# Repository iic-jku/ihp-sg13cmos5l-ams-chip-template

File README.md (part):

<!-- template-only -->
# An Open-Source Analog Mixed-Signal Chip Design Template & Tutorial for the ihp-sg13cmos5l Open-PDK

(c) 2026 Simon Dorrer and Harald Pretl

Institute for Integrated Circuits and Quantum Computing, Johannes Kepler University (JKU), Linz, Austria

<!-- /template-only -->
> [!IMPORTANT]
> This repository requires the [IIC-OSIC-TOOLS](https://github.com/iic-jku/IIC-OSIC-TOOLS) container with tag `2026.11` or later.

<!-- template-only -->
<p align="center">
  
  <br>
  <em>Chip render of the ihp-sg13cmos5l analog mixed-signal template chip (1.6 mm x 1.6 mm).</em>
</p>

<p align="center">
  
  <br>
  <em>Render of the TopMetal1 AMS Chip logo, generated with the tool ArtistIC.</em>
</p>

## Overview

Developing high-performance open-source silicon requires both the availability of tapeout-ready open-PDKs and robust, user-friendly EDA flows. While digital RTL-to-GDS flows offer an easy entry with documentation and examples, analog mixed-signal (AMS) design still suffers from a steep learning curve and the lack of examples and instructions. This repository provides a comprehensive template and tutorial for AMS chip design using the ihp-sg13cmos5l Open-PDK, guiding the designer from initial system-level specifications to the tapeout-ready chip.

This Makefile-driven repository simulates, builds, and fully verifies (DRC, LVS, PEX) a complete analog mixed-signal chip for the ihp-sg13cmos5l Open-PDK, including padframe generation, top-level assembly and bondplan generation. The flow uses:

- [**LibreLane**](https://github.com/librelane/librelane) for digital macro hardening, padframe generation, top-level assembly, filler and logo insertion
- [**Xschem**](https://github.com/StefanSchippers/xschem) for schematic entry
- [**Ngspice**](https://github.com/danchitnis/ngspice-sf-mirror), [**VACASK**](https://codeberg.org/arpadbuermen/VACASK) and [**CACE**](https://github.com/fossi-foundation/cace) for analog simulation
- [**KLayout**](https://github.com/KLayout/klayout) for viewing and routing of the layout
- [**Magic**](https://github.com/rtimothyedwards/magic) + [**Netgen**](https://github.com/rtimothyedwards/netgen) and [**KLayout**](https://github.com/KLayout/klayout) for DRC, LVS and PEX verification
- [**gdscheck**](https://github.com/aesc-silicon/gdscheck) as a third, standalone DRC engine with its own rule decks
- **SystemVerilog**, [**Verilator**](https://github.com/verilator/verilator), [**iverilog**](https://github.com/steveicarus/iverilog), [**cocotb**](https://github.com/cocotb/cocotb), [**GTKWave**](https://github.com/gtkwave/gtkwave) and [**Surfer**](https://gitlab.com/surfer-project/surfer) for linting and simulation of digital macros

The repository is the starting point for your own custom silicon and provides a universal design flow solution: Just clone the repo, enter the IIC-OSIC-TOOLS container, and run `make all` to get a tapeout-ready analog mixed-signal chip. Focus on your design and do not worry about the tools and the design flow!

Furthermore, it serves as a regression test for the above-mentioned open-source tools and their dependencies using the ihp-sg13cmos5l Open-PDK.

## PDKs

This template is available for the following open-source PDKs:
- **ihp-sg13g2**: [ihp-sg13g2-ams-chip-template](https://github.com/iic-jku/ihp-sg13g2-ams-chip-template)
- **ihp-sg13cmos5l**: this repository
- **sky130A**: [sky130A-ams-chip-template](https://github.com/iic-jku/sky130A-ams-chip-template)
- **gf180mcuD**: [gf180mcuD-ams-chip-template](https://github.com/iic-jku/gf180mcuD-ams-chip-template)

## Tutorial

A step-by-step tutorial, including additional exercises, can be found [here](https://iic-jku.github.io/ihp-sg13cmos5l-ams-chip-template/index.html). It is the SG13CMOS5L version of the [tutorial](https://iic-jku.github.io/ihp-sg13g2-ams-chip-template/index.html) of the SG13G2 sibling of this template.

An overview of the open-source IC design landscape is presented [here](https://ic3.ie/resources/open-source-ic-design-day).

Are you interested in an open-source RFIC flow? Check it out [here](https://github.com/iic-jku/SG13CMOS_SPARX).

## Examples

Examples based on the SG13G2 sibling of this template are:
- [TinyWhisper](https://github.com/iic-jku/TinyWhisper): An Open-Source Fully-Integrated Multi-Mode Short-Wave Transmitter for Amateur Radio Applications in 130-nm CMOS
- [SPARX](https://github.com/iic-jku/SG13CMOS_SPARX): An Open-Source, Automated, Programmatically Generated, Frequency-Scalable Six-Port Receiver in 130-nm CMOS
- [Multi-Project Chip](https://github.com/iic-jku/gf180mcu-jku-projects) for the wafer.space gf180mcuD MPW run

<!-- /template-only -->
## Chip Documentation

A designer-oriented description of this chip can be found in [doc/](doc/):

- **[doc/specifications.md](doc/specifications.md)**: top-level specifications (technology, supplies, clock, macro inventory, functional behaviour).
- **[doc/pinout.md](doc/pinout.md)**: full 32-pad bondpad table per side, with the `chip_top` port and the role each pad carries inside `chip_core`.
- **[doc/floorplan.md](doc/floorplan.md)**: die / core geometry, hard-macro placement coordinates, PDN strategy and the floorplan diagram.

Measurements of the fabricated chip go into [measurements/](measurements/), one folder per taped-out release.

## Directory Structure

<details>
<summary>Show Directory Structure</summary>

```text
📁 ihp-sg13cmos5l-ams-chip-template/
├─ 📁 .github/
│  └─ 📁 workflows/
│     ├─ license-check.yml
│     ├─ quarto-publish.yml
│     └─ regression.yml
├─ 📁 doc/
│  ├─ 📁 ihp-sg13cmos5l-Open-PDK/
│  ├─ 📁 ihp-structure-proposals/
│  ├─ 📁 klayout/
│  ├─ 📁 librelane/
│  ├─ 📁 prep-ic/
│  ├─ 📁 sizing/
│  ├─ 📁 verilog/
│  ├─ floorplan.md
│  ├─ pinout.md
│  ├─ README.md
│  └─ specifications.md
├─ 📁 flow/
│  ├─ 📁 artistic/
│  ├─ 📁 librelane/
│  │  ├─ 📁 plugins/
│  │  │  └─ librelane_plugin_chip_finish.py
│  │  ├─ chip_top.sdc
│  │  ├─ config.yaml
│  │  └─ pdn_cfg.tcl
│  └─ 📁 logo/
│     └─ chip_logo_mono.png
├─ 📁 ip/
│  ├─ 📁 sg13cmos5l_io_custom/
│  ├─ 📁 sg13cmos5l_ip__bondpad_70x70/
│  │  ├─ 📁 final/
│  │  ├─ 📁 script/
│  │  ├─ 📁 verification/
│  │  ├─ Makefile
│  │  └─ README.md
│  ├─ 📁 sg13cmos5l_ip__rfpad_70x70/
│  │  ├─ 📁 final/
│  │  ├─ 📁 netlist/
│  │  ├─ 📁 schematic/
│  │  ├─ 📁 script/
│  │  ├─ 📁 verification/
│  │  ├─ Makefile
│  │  └─ README.md
│  ├─ 📁 sg13cmos5l_ip__jku/
│  │  ├─ 📁 final/
│  │  ├─ 📁 logo/
│  │  ├─ 📁 script/
│  │  ├─ 📁 verification/
│  │  ├─ Makefile
│  │  └─ README.md
│  ├─ 📁 sg13cmos5l_ip__jku_names/
│  │  ├─ 📁 final/
│  │  ├─ 📁 logo/
│  │  ├─ 📁 script/
│  │  ├─ 📁 verification/
│  │  ├─ Makefile
│  │  └─ README.md
│  └─ 📁 sg13cmos5l_ip__template_name/
│     ├─ 📁 final/
│     ├─ 📁 logo/
│     ├─ 📁 script/
│     ├─ 📁 verification/
│     ├─ Makefile
│     └─ README.md
├─ 📁 layout/
│  ├─ chip_top.gds.gz
│  └─ chip_top_logo_fill.gds.gz
├─ 📁 LICENSES/
│  ├─ Apache-2.0.txt
│  ├─ LicenseRef-EUROPRACTICE.txt
│  └─ SHL-2.1.txt
├─ 📁 macros/
│  ├─ 📁 counter/
│  │  ├─ 📁 final/
│  │  ├─ 📁 flow/
│  │  ├─ 📁 fpga/
│  │  ├─ 📁 netlist/
│  │  ├─ 📁 render/
│  │  ├─ 📁 rtl/
│  │  ├─ 📁 schematic/
│  │  ├─ 📁 scripts/
│  │  ├─ 📁 testbenches/
│  │  ├─ 📁 verification/
│  │  ├─ Makefile
│  │  └─ README.md
│  ├─ 📁 inverter/
│  │  ├─ 📁 final/
│  │  ├─ 📁 layout/
│  │  ├─ 📁 netlist/
│  │  ├─ 📁 render/
│  │  ├─ 📁 schematic/
│  │  ├─ 📁 scripts/
│  │  ├─ 📁 testbenches/
│  │  ├─ 📁 verification/
│  │  ├─ Makefile
│  │  └─ README.md
│  ├─ 📁 scripts/
│  ├─ 📁 vco/
│  │  ├─ 📁 final/
│  │  ├─ 📁 layout/
│  │  ├─ 📁 netlist/
│  │  ├─ 📁 render/
│  │  ├─ 📁 schematic/
│  │  ├─ 📁 scripts/
│  │  ├─ 📁 testbenches/
│  │  ├─ 📁 verification/
│  │  ├─ Makefile
│  │  └─ README.md
│  ├─ Makefile
│  └─ README.md
├─ 📁 measurements/
│  ├─ 📁 v.1.0.0/
│  │  ├─ 📁 amplifier/
│  │  ├─ 📁 chip/
│  │  ├─ 📁 counters/
│  │  ├─ 📁 inverter/
│  │  ├─ 📁 ringosc/
│  │  ├─ 📁 vco/
│  │  └─ README.md
│  └─ README.md
├─ 📁 netlist/
│  ├─ 📁 layout/
│  ├─ 📁 nl/
│  ├─ 📁 pex/
│  ├─ 📁 pnl/
│  ├─ 📁 schematic/
│  ├─ 📁 sdc/
│  ├─ 📁 spef/
│  └─ 📁 spice/
├─ 📁 packaging/
│  ├─ 📁 layout/
│  │  ├─ chip_top_bondplan.gds
│  │  ├─ chip_top_logo_TM1.gds.gz
│  │  ├─ EP_PACKAGES_08022018.gds
│  │  └─ OP_QFN32_A4_FIT.gds
│  ├─ 📁 render/
│  │  └─ chip_top_bondplan_{white,black}.{png,svg}
│  ├─ 📁 scripts/
│  │  └─ run_bondplan.py
│  ├─ config.yaml
│  ├─ README.md
│  └─ result.md
├─ 📁 release/
│  └─ 📁 v.1.0.0/
│     ├─ 📁 gds/
│     ├─ 📁 img/
│     └─ 📁 netlist/
├─ 📁 render/
│  ├─ 📁 blender/
│  └─ 📁 img/
├─ 📁 rtl/
│  ├─ chip_core.sv
│  └─ chip_top.sv
├─ 📁 schematic/
│  └─ 📁 xschem/
│     ├─ chip_top.sch
│     ├─ chip_top.sym
│     ├─ chip_top_pex.sym
│     └─ xschemrc
├─ 📁 scripts/
│  ├─ check_pex_ports.py
│  └─ sim_gl_power.tcl
├─ 📁 testbenches/
│  ├─ 📁 cocotb/
│  │  ├─ chip_top_tb.gtkw
│  │  ├─ chip_top_tb.py
│  │  └─ chip_top_tb.surf.ron
│  └─ 📁 xschem/
│     ├─ 📁 plot_simulations/
│     │  ├─ 📁 data/
│     │  ├─ 📁 figures/
│     │  ├─ ngspice2python.py
│     │  └─ plot_chip_top.py
│     ├─ chip_top_tb_tran.sch
│     └─ xschemrc
├─ 📁 tutorial/
│  ├─ 📁 fig/
│  ├─ _quarto.yml
│  ├─ index.qmd
│  ├─ Makefile
│  └─ requirements.txt
├─ 📁 verification/
│  ├─ 📁 drc/
│  ├─ 📁 lvs/
│  └─ 📁 reports/
│     ├─ antenna_summary.rpt
│     ├─ antenna_violations.rpt
│     ├─ irdrop.rpt
│     ├─ lvs.netgen.rpt
│     ├─ manufacturability.rpt
│     ├─ sim_gl_power_cocotb.rpt
│     ├─ stapostpnr_*.rpt
│     ├─ stat.rpt
│     ├─ yosys_post_dff.rpt
│     ├─ yosys_pre_techmap.rpt
│     └─ yosys_synth_check.rpt
├─ CITATION.cff
├─ LICENSE
├─ Makefile
├─ README.md
├─ REUSE.toml
└─ ToDo.md
```

</details>

## Xschem Configuration

Xschem reads exactly one `xschemrc` at start-up, and that file decides which symbol libraries are visible and where netlists and simulation output are written. This repository ships one per folder that holds schematics:

| `xschemrc` | Belongs to |
| --- | --- |
| [`schematic/xschem/xschemrc`](schematic/xschem/xschemrc) | chip top-level schematics |
| [`testbenches/xschem/xschemrc`](testbenches/xschem/xschemrc) | chip top-level testbenches |
| [`ip/sg13cmos5l_ip__rfpad_70x70/schematic/xschem/xschemrc`](ip/sg13cmos5l_ip__rfpad_70x70/schematic/xschem/xschemrc) | RF pad schematic |
| [`macros/inverter/schematic/xschem/xschemrc`](macros/inverter/schematic/xschem/xschemrc) | inverter schematics |
| [`macros/inverter/testbenches/xschem/xschemrc`](macros/inverter/testbenches/xschem/xschemrc) | inverter testbenches |
| [`macros/inverter/verification/cace/templates/xschemrc`](macros/inverter/verification/cace/templates/xschemrc) | CACE testbench templates |
| [`macros/counter/schematic/xschem/xschemrc`](macros/counter/schematic/xschem/xschemrc) | counter schematics |
| [`macros/counter/testbenches/xschem/xschemrc`](macros/counter/testbenches/xschem/xschemrc) | counter testbenches |
| [`macros/vco/schematic/xschem/xschemrc`](macros/vco/schematic/xschem/xschemrc) | VCO schematics |
| [`macros/vco/testbenches/xschem/xschemrc`](macros/vco/testbenches/xschem/xschemrc) | VCO testbenches |

### What Every File Does

All of them run the same four steps, in this order:

1. **Pick the PDK.** `PDK_ROOT` is probed in the usual install locations if the environment does not set it, and `PDK` falls back to `ihp-sg13cmos5l`. The container already exports `PDK_ROOT`, and [`.designinit`](.designinit) exports `PDK`, so this step is only a safety net for an Xschem started outside that environment.
2. **Source the PDK `xschemrc`.** `$PDK_ROOT/$PDK/libs.tech/xschem/xschemrc` brings in the IHP device symbols, the ngspice model paths and the IHP menu. It is guarded by `[info exists PDK]` so it is read once even when several project files are chained.
3. **Add the project library paths.** `append_xschem_library_path_unique` appends a folder to `XSCHEM_LIBRARY_PATH` only if it is not already there, so the same folder never appears twice no matter how the files are chained. [`testbenches/xschem/xschemrc`](testbenches/xschem/xschemrc) adds none of its own and gets its paths from the file it sources.
4. **Pin the netlist directory.** `pin_netlist_dir` decides where `xschem netlist` and the simulators write.

Both helper procedures are defined behind an `[info commands ...]` guard, so sourcing one file from another is harmless and the order does not matter.

### How the Files Are Chained

The chip top-level pulls in everything below it:

```text
testbenches/xschem/xschemrc
└─ source schematic/xschem/xschemrc
   ├─ source macros/inverter/schematic/xschem/xschemrc
   └─ source macros/counter/schematic/xschem/xschemrc

macros/inverter/verification/cace/templates/xschemrc
└─ source macros/inverter/schematic/xschem/xschemrc
```

Each schematic folder puts itself and its sibling testbenches folder on the library path, and each testbenches folder does the reverse. The chip top-level therefore sees all six schematic and testbench folders, which is what lets `chip_top.sch` instantiate `inverter_top.sym` and `counter_top.sym`, and what lets you open a macro testbench from a chip top-level session. The macro files do not source each other, so a macro can be opened and simulated on its own without the top level being present.

### Where Netlists and Simulation Output Go

`pin_netlist_dir` maps the folder of the schematic being netlisted to a `simulations/` folder:

| Schematic lives in | `netlist_dir` |
| --- | --- |
| `<x>/testbenches/xschem` | `<x>/testbenches/xschem/simulations` |
| `<x>/schematic/xschem` | `<x>/testbenches/xschem/simulations` |
| `.../cace/templates` | `.../cace/templates/simulations` |
| anywhere else (a PDK example) | left at the value the `xschemrc` pinned |

It runs twice: once while the `xschemrc` is read, using that file's own folder, and again through Xschem's `load_file_postprocess` hook for every schematic that is opened afterwards. The second call is the important one. Because the chip top-level puts the macro folders on the library path, a macro testbench can be opened from a chip top-level session, and without the hook its netlist would land in `testbenches/xschem/simulations/`. Its relative includes such as `.include ../../../netlist/pex/inverter_magic_pex_3.spice` are resolved by ngspice relative to the netlist file, so they would then point at the wrong tree and the simulation would abort. With the hook, the netlist always lands next to its own schematic and the includes resolve.

A `set netlist_dir` passed on the Xschem command line still wins, because `--command` runs after the file is loaded. The LVS netlist targets rely on this to write into `netlist/schematic/` instead.

All `simulations/` folders are generated and git-ignored.

### Which File Is Used

- The Makefile targets always name one explicitly with `--rcfile`, so a target behaves the same from any working directory.
- Inside the container, [`.designinit`](.designinit) only exports the PDK variables. It does not wrap `xschem`, so a plain `xschem <file>` uses whatever the current directory provides.
- Starting Xschem from within one of the folders in the table above picks up that folder's file, which is the normal interactive case.
- `make open` starts Xschem in the file's own directory, so the same rule applies to every button of the file browser, see [Open the Design Files](#open-the-design-files).

## Makefile Structure

The whole flow is driven by Makefiles. The top-level `Makefile` builds the chip, and every component under [`macros/`](macros/) and [`ip/`](ip/) has its own `Makefile` and `README.md` following the same conventions (`make help`, `make all`, and so on). You can run each component from the top level or directly from inside its own folder. The figure below shows how the targets are connected when you run `make all` at the top level.

<p align="center">
  
  <br>
  <em>Overview of the Makefile targets.</em>
</p>

Every coloured branch corresponds to one deliverable (top chip, bondpad, RF pad, logos, digital macro, analog macro, packaging). The grey targets connect `make all` to those branches.

Solid arrows are direct `$(MAKE) <target>` calls within a single Makefile. Dashed arrows descend into a subdirectory, either as a recursive `$(MAKE) -C <dir> all` call into a sub-Makefile or as the Python bondplan flow in `packaging/`. The numbers on the second level give the execution order of `make all`, and the vertical order inside the coloured boxes gives the execution order of each sub-Makefile.

At the top level, `make all` runs four steps in this order:

1. `build-all` initialises the submodules and builds every component by calling its own `all` target: bondpad, RF pad, logos, digital macro, analog macro, and finally the chip assembly with `build-top` (LibreLane, copy-back of all artifacts, logo and fill insertion, final GDS render).
2. `klayout-drc-regular` (the sign-off deck) and `gdscheck-drc-regular` run the DRC of the final `chip_top_logo_fill` GDS. A violation stops `make all` (see [Design Rule Check (DRC)](#design-rule-check-drc)). `magic-drc` is left out until IHP's IO pads and SRAM are clean in Magic.
3. `sim-all` runs the top-level RTL and gate-level simulations on the netlists produced by this build.
4. `bondplan` generates the bonding diagram, the bondwires, and the pin table.

Every component follows the same principle. The simulations always run last, so they use the artifacts that the same invocation has just produced.

| Makefile | `all` flow |
| --- | --- |
| [`macros/counter/`](macros/counter/) (digital) | lint -> build (FPGA and LibreLane, including the XSPICE model) -> extract (PEX of the hardened GDS) -> simulate. DRC and LVS run inside the LibreLane flow. |
| [`macros/inverter/`](macros/inverter/) (analog) | verify (DRC, LVS, PEX) -> build (LEF, LIB, Verilog stub, GDS, render) -> simulate |
| [`macros/vco/`](macros/vco/) (RF) | layouts (KLayout Python scripts) -> coil EM (Palace) -> lumped-element model (snp2le) -> verify (DRC, LVS, PEX) -> build (LEF, LIB, Verilog stub, GDS, render) -> simulate (ngspice and VACASK). Not part of the chip build yet. |
| [`ip/*`](ip/) (bondpad, RF pad, logos) | build -> verify (DRC, and LVS on the RF pad) |
| top level | build -> verify (DRC) -> simulate -> package |

The following sections describe the top-level targets in detail. The macro and IP targets are documented in the `README.md` of the respective subfolder.

## Makefile Targets

### Show Available Targets

The default Make target is `help`, so running `make` prints usage and all available targets with short descriptions.

```sh
make
make help
```

### PDK Guard

Every target except `help`, `clean` and `clean-all` needs the `ihp-sg13cmos5l` PDK. The container starts with `ihp-sg13g2` selected, so the wrong PDK is the default state here, and it silently mixes technologies: LibreLane hardens against the wrong tech LEF and standard cells, DRC and LVS run against the wrong rule deck, Magic reads the wrong `magicrc`, and the results look valid. The Makefile therefore compares `$PDK` against `REQUIRED_PDK` once when it is parsed, before any target runs:

```sh
$ make librelane
Makefile:27: *** PDK is "ihp-sg13g2", but this chip needs "ihp-sg13cmos5l". Run `sak-pdk ihp-sg13cmos5l` in this shell and retry, or pass REQUIRED_PDK= to skip this check.  Stop.
```

The check is a parse-time conditional at the top of the Makefile, not a prerequisite of each target, so it costs nothing and cannot be forgotten when a target is added. `help`, `clean` and `clean-all` are exempt, so the usage text and the cleanup still work under any PDK. The macro and IP Makefiles carry the same guard, so the recursive `make -C` calls of `build-all` are checked as well.

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
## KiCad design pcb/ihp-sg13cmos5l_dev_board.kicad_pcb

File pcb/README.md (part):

# IHP SG13CMOS5L dev board

KiCad 10 project of the development and test board of the chip taped out from branch `IHP-TO-2026-11` (IHP submission SoC1693), in its EUROPRACTICE QFN32 Open-Pak.
The board is made for hand soldering: passives are 0603 or larger, the ICs are leaded, the chip's lands reach 0.55 mm beyond its body, and its exposed pad is soldered from the bottom through a plated hole.
A Raspberry Pi Pico H on sockets is the host, with the GPIO map of the Tiny Tapeout demo board firmware. Every chip supply has its own LDO, a bench jack, a current jumper and an INA226, the analog pins come out on BNC and on a header, and the two VCO outputs on SMA.

## Files

| File | Contents |
| --- | --- |
| `ihp-sg13cmos5l_dev_board.kicad_pro` | Project: net classes (`RF_50`, `Power`, `Default`), design rules, track and via presets |
| `ihp-sg13cmos5l_dev_board.kicad_sch` | Root sheet: the chip, its decoupling, the series resistors of the outputs, mechanics |
| `power.kicad_sch` | USB input, 3.3 V auxiliary rail, `IOVDD` and `VDD` domains |
| `macros.kicad_sch` | `VDD_RF`, `VDD_RO` and `VDD_HV` domains, ring oscillator on/off |
| `host.kicad_sch` | Pico, level translators, clock sources and select, reset, count LEDs, headers |
| `analog.kicad_sch` | DAC, `vtune`, amplifier, inverter and ring oscillator front ends, buffers to the Pico ADC |
| `rf.kicad_sch` | VCO outputs and the reference line |
| `ihp-sg13cmos5l_dev_board.kicad_pcb` | Board, revision 0.1 |
| `ihp-sg13cmos5l_dev_board.kicad_dru` | Custom rules: the stricter value of JLCPCB and Aisler per rule, house rules, RF line and launch rules |
| `lib/` | Project symbols (chip, Pico H, TLV3544, ECS-3225MV) and footprints (QFN32 for hand soldering, Cinch SMA, Pico sockets, BNC with its silkscreen inside the board edge, tip jacks, logos), 3D models of the tip jacks |
| `render/` | Renders of the board |

Stock parts use the KiCad 10 libraries, and their 3D models resolve through `${KICAD10_3DMODEL_DIR}`. The Cinch SMA has no model there, so its footprint shows the Samtec edge-mount SMA instead. Every part carries `Manufacturer` and `MPN` fields.

## The chip on the board

The pin map is `packaging/config.yaml` of `ihp-sg13cmos5l-ams-chip-template @ 7bd9690` (branch `IHP-TO-2026-11`): pins 1 to 8 down the left side, 9 to 16 left to right along the bottom, 17 to 24 up the right side, 25 to 32 right to left along the top. The symbol `SoC1693` draws the pins where the package has them.

| Side | Pins | Board nets |
| --- | --- | --- |
| Left | 1 to 8 | `CLK`, `RST_N`, `SEL1`, `SEL0`, `IOVDD`, GND, `VDD`, GND |
| Bottom | 9 to 16 | `DI_EN`, `VTUNE`, GND, `RF_OUT_N`, `RF_OUT_P`, GND, `VDD_RF`, GND |
| Right | 17 to 24 | `AMP_VIN`, `AMP_VOUT`, `INV_VIN`, `INV_VOUT`, `inv_dout` (33 Ω series), `VDD_RO`, `RO_VOUT`, `VDD_HV` |
| Top | 25 to 32 | `count[7]` down to `count[0]`, each through a 33 Ω series resistor |

The footprint follows QP Technologies' `QP-QFN32-5MM-0.50MM` (drawing 500384 rev A), the part EUROPRACTICE's Open-Pak QFN32 matches: 5 × 5 mm body, 0.5 mm pitch, terminals 0.23 × 0.32 mm, exposed pad 3.2 mm. The lands are 0.25 mm wide and run from 2.05 to 3.05 mm from the centre, 0.55 mm beyond the body for the iron. The exposed pad is GND (conductive die attach on the substrate) and carries a 1.0 mm plated hole, so it can be soldered from the bottom side.

`di_en`, `vtune` and `vdd_rf` sit between the RF pins and the corners, so each leaves through a via right at its pin. The chip's decoupling (100 nF and 100 pF per supply pin, 10 nF on `vtune`) sits on the bottom side under its pins, the 10 µF of each domain after its shunt.

## Supplies

Power comes from the Pico's USB (`VBUS`) through a ferrite. An AP2112K makes 3.3 V for the board logic (translators, DAC, INA226, buffers, LEDs). Each chip domain has its own LT3042:

| Domain | Pin | Default | Set points | Shunt | INA226 | Jack |
| --- | --- | --- | --- | --- | --- | --- |
| `IOVDD` | 5 | 3.32 V | fixed | 4.7 Ω | 0x40 | yellow |
| `VDD` | 7 | 1.2 V | 1.5, 1.35, 1.2 V, 1.65 V open | 10 Ω | 0x41 | red |
| `VDD_RF` | 15 | 1.5 V | 1.5, 1.35, 1.2 V, 1.65 V open | 1 Ω | 0x44 | red |
| `VDD_RO` | 22 | 1.2 V | 1.5, 1.35, 1.2 V, 1.65 V open, off | 4.7 Ω | 0x45 | red |
| `VDD_HV` | 24 | 1.2 V | 1.5, 1.35, 1.2 V, 1.65 V open | 10 Ω | 0x42 | red |

- **Set points.** The base `R_SET` (16.5 kΩ, 100 µA from the SET pin) gives 1.65 V, the highest any of these pins may see. Each set-point jumper adds a resistor in parallel (165 kΩ, 75 kΩ and 44.2 kΩ for 1.5, 1.35 and 1.2 V), so a missing or moved jumper can only lower a rail.
- **Current limit.** 2.49 kΩ on `ILIM` limits every domain to 50 mA.
- **Order.** The chip's specification asks for `IOVDD` first and the ring `VDD` no later than `vdd_rf`. The enables are chained by power good: `IOVDD` (power good at 3.03 V) enables `VDD`, `VDD` (power good at 1.0 V) enables `VDD_RF`, `VDD_RO` and `VDD_HV`. The last three tie `PGFB` to their input, which disables power good and the fast start-up.
- **Source jumper** (1-2 fitted): 1-2 takes the LT3042, 2-3 the tip jack. A bench supply on a jack bypasses the power-up order and the current limit: bring `IOVDD` up first by hand, and keep the red jacks at or below 1.65 V.
- **Current jumper** (fitted): remove it for an ammeter. The INA226 reads the shunt behind it and the rail voltage at the chip side, over I2C.
- **`IOVDD_SRC`.** The translators' `IOVDD` side, the oscillator and the pull-ups take their supply ahead of the `IOVDD` current jumper, so the `IOVDD` reading is the chip alone.
- **Ring oscillator** (`JP370`): 1-2 on, 2-3 off (`VDD_RO` at 0 V, since the ring oscillator has no enable of its own).
- Every domain has a 2-pin voltage header (signal and GND).

## Host

A Raspberry Pi Pico H (RP2040) plugs into two 1x20 sockets, USB towards the left edge. Its GPIO use follows `GPIOMapTT06` of the Tiny Tapeout MicroPython firmware v2.x, so clock, reset, `ui_in` and `uo_out` sit where that SDK expects them (the TT project mux on GP2 to GP4 has no counterpart here):

| GPIO | TT name | Board use |
| --- | --- | --- |
| GP0 | `RP_PROJCLK` | `clk` (through the translator to `CLK_SEL` 3-4) |
| GP1 | `PROJECT_nRST` | `rst_n` |
| GP9, GP10, GP11 | `ui_in[0..2]` | `sel[0]`, `sel[1]`, `di_en` |
| GP5 to GP8, GP13 to GP16 | `uo_out[0..7]` | `count[0]` to `count[7]` |
| GP21 | `uio[0]` | `inv_dout` |
| GP18, GP19 | | I2C1 SDA, SCL (five INA226, MCP4728 at 0x60) |
| GP26, GP27, GP28 | | ADC: buffered `amp_vout`, `inv_vout` and `vtune` |
| GP2 to GP4, GP12, GP17, GP20, GP22 | | spare, on the `EXP` header `J406` |

- SN74LVC8T245 and SN74LVC1T45 translate between the Pico's 3.3 V and `IOVDD`. They isolate (Ioff) when either side is off, so the chip is never back-powered and `IOVDD` can be swept.
- Without the Pico the pull resistors hold `rst_n` high, `sel = 00` (no counter clocked), `di_en` low (VCO off) and the clock low.
- The chip's `sel` may change only with `rst_n` low or the clock stopped, and a counter resets only while selected and clocked (`doc/specifications.md` of the TO branch).
- Buttons: `PICO RUN` resets the Pico, `RESET` pulls `rst_n` low, `STEP` gives one clock edge per press (selected on `CLK_SEL` 7-8).
- Slow-clock demo: eight green LEDs show `count[7:0]` from the 3.3 V side of the translator, and removing `JP402` switches them off.
- `LA` header `J405`: odd pins `count[0]` to `count[7]`, `inv_dout` (all 3.3 V side) and the chip clock through 100 Ω, even pins GND.

## Clock

`CLK_SEL` (`J403`) takes one jumper:

| Jumper | Source |
| --- | --- |
| 1-2 | 50 MHz oscillator ECS-3225MV (on `IOVDD_SRC`, stopped by fitting `JP401`) |
| 3-4 | Pico GP0 |
| 5-6 | BNC `CLK_EXT`: 100 Ω in series, clamped to GND and `IOVDD`, 49.9 Ω termination `R411` not fitted |
| 7-8 | `STEP` button, debounced (RC and 74LVC1G14) |

Each source has its own 33 Ω series resistor, and the chip input has 100 kΩ to GND.

## Analog

| Signal | Board path |
| --- | --- |
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
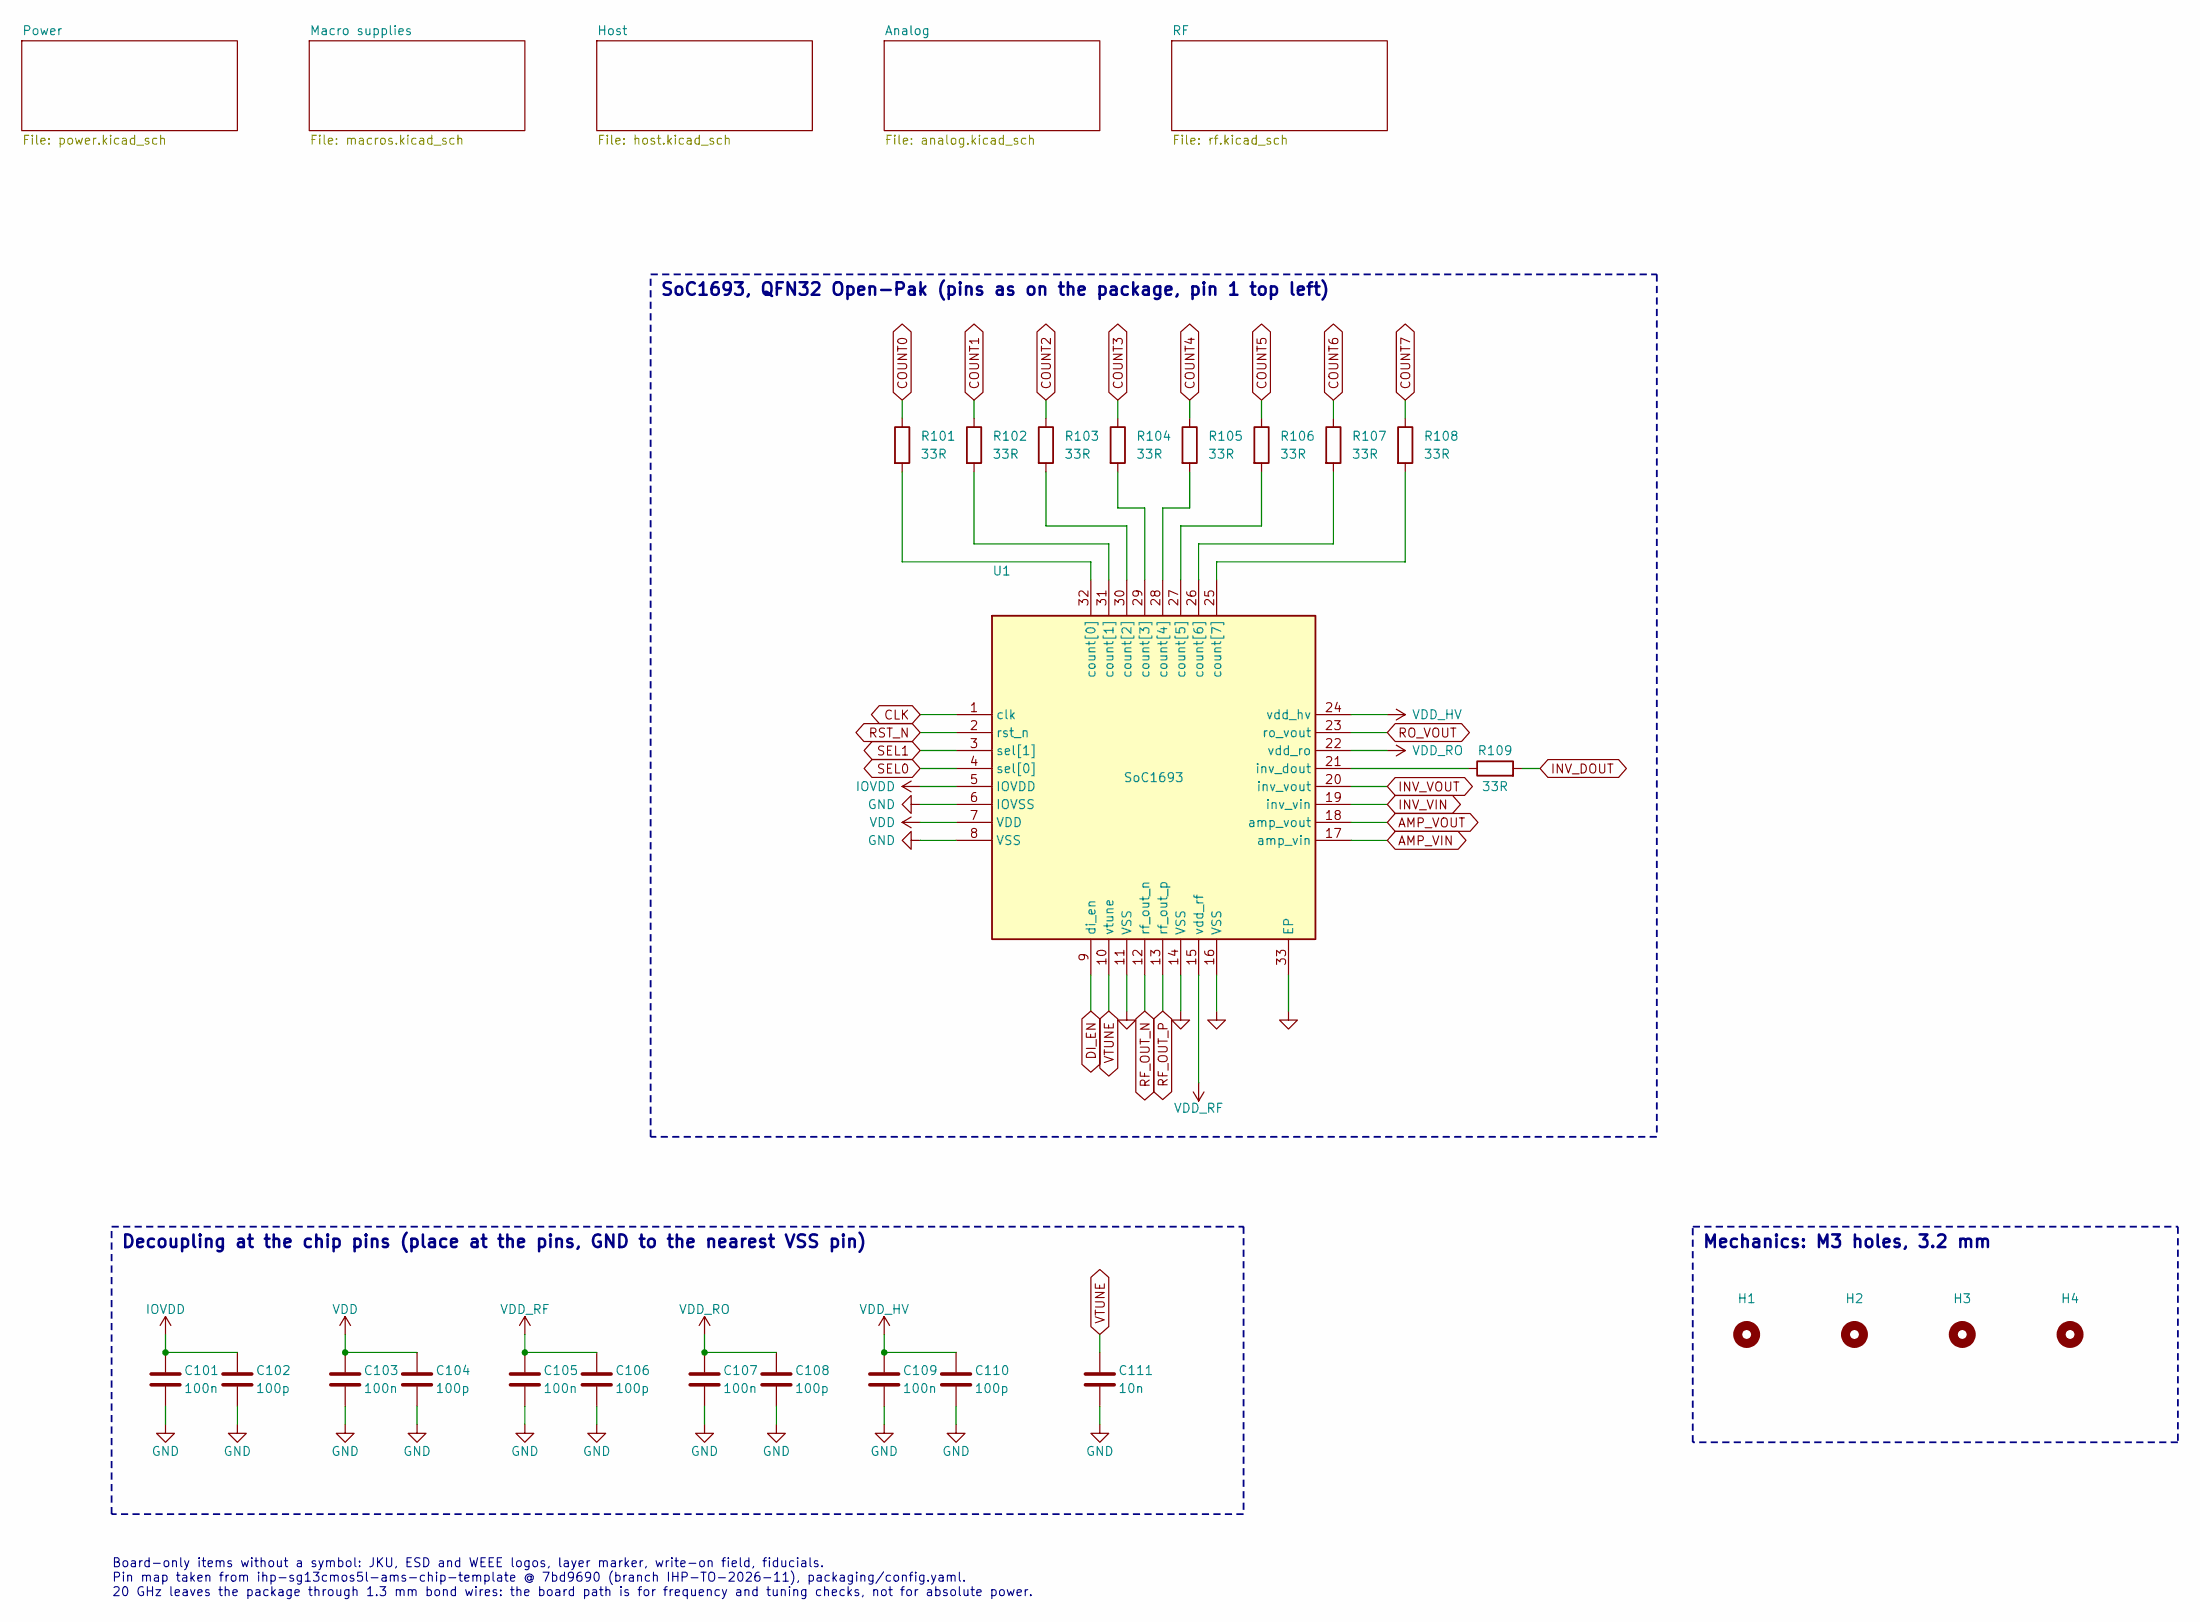
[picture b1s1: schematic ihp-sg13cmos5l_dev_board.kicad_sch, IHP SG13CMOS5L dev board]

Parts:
C101, C103, C105, C107, C109: 100n; C_0603_1608Metric_Pad1.08x0.95mm_HandSolder; MPN CL10B104KB8NNNC
C102, C104, C106, C108, C110: 100p; C_0603_1608Metric_Pad1.08x0.95mm_HandSolder; MPN CL10C101JB8NNNC
C111: 10n; C_0603_1608Metric_Pad1.08x0.95mm_HandSolder; MPN GRM1885C1H103JA01D
H1, H2, H3, H4: MountingHole_M3; MountingHole_3.2mm_M3
R101, R102, R103, R104, R105, R106, R107, R108, R109: 33R; R_0603_1608Metric_Pad0.98x0.95mm_HandSolder; MPN RC0603FR-0733RL
U1: SoC1693; QFN-32-1EP_5x5mm_P0.5mm_EP3.2x3.2mm_OpenPak_HandSolder

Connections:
AMP_VIN: U1.17 (amp_vin); also elsewhere on the board
AMP_VOUT: U1.18 (amp_vout); also elsewhere on the board
CLK: U1.1 (clk); also elsewhere on the board
COUNT0: R101.1; also elsewhere on the board
COUNT1: R102.1; also elsewhere on the board
COUNT2: R103.1; also elsewhere on the board
COUNT3: R104.1; also elsewhere on the board
COUNT4: R105.1; also elsewhere on the board
COUNT5: R106.1; also elsewhere on the board
COUNT6: R107.1; also elsewhere on the board
COUNT7: R108.1; also elsewhere on the board
DI_EN: U1.9 (di_en); also elsewhere on the board
GND: C101.2, C102.2, C103.2, C104.2, C105.2, C106.2, C107.2, C108.2, C109.2, C110.2, C111.2, U1.6 (IOVSS), U1.8 (VSS), U1.11 (VSS), U1.14 (VSS), U1.16 (VSS), U1.33 (EP); also elsewhere on the board
INV_DOUT: R109.2; also elsewhere on the board
INV_VIN: U1.19 (inv_vin); also elsewhere on the board
INV_VOUT: U1.20 (inv_vout); also elsewhere on the board
IOVDD: C101.1, C102.1, U1.5 (IOVDD); also elsewhere on the board
unnamed: R101.2, U1.32 (count[0])
unnamed: R102.2, U1.31 (count[1])
unnamed: R103.2, U1.30 (count[2])
unnamed: R104.2, U1.29 (count[3])
unnamed: R105.2, U1.28 (count[4])
unnamed: R106.2, U1.27 (count[5])
unnamed: R107.2, U1.26 (count[6])
unnamed: R108.2, U1.25 (count[7])
unnamed: R109.1, U1.21 (inv_dout)
RF_OUT_N: U1.12 (rf_out_n); also elsewhere on the board
RF_OUT_P: U1.13 (rf_out_p); also elsewhere on the board
RO_VOUT: U1.23 (ro_vout); also elsewhere on the board
RST_N: U1.2 (rst_n); also elsewhere on the board
SEL0: U1.4 (sel[0]); also elsewhere on the board
SEL1: U1.3 (sel[1]); also elsewhere on the board
VDD: C103.1, C104.1, U1.7 (VDD); also elsewhere on the board
VDD_HV: C109.1, C110.1, U1.24 (vdd_hv); also elsewhere on the board
VDD_RF: C105.1, C106.1, U1.15 (vdd_rf); also elsewhere on the board
VDD_RO: C107.1, C108.1, U1.22 (vdd_ro); also elsewhere on the board
VTUNE: C111.1, U1.10 (vtune); also elsewhere on the board

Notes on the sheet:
SoC1693, QFN32 Open-Pak (pins as on the package, pin 1 top left)
Decoupling at the chip pins (place at the pins, GND to the nearest VSS pin)
Mechanics: M3 holes, 3.2 mm
Board-only items without a symbol: JKU, ESD and WEEE logos, layer marker, write-on field, fiducials. Pin map taken from ihp-sg13cmos5l-ams-chip-template @ 7bd9690 (branch IHP-TO-2026-11), packaging/config.yaml. 20 GHz leaves the package through 1.3 mm bond wires: the board path is for frequency and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

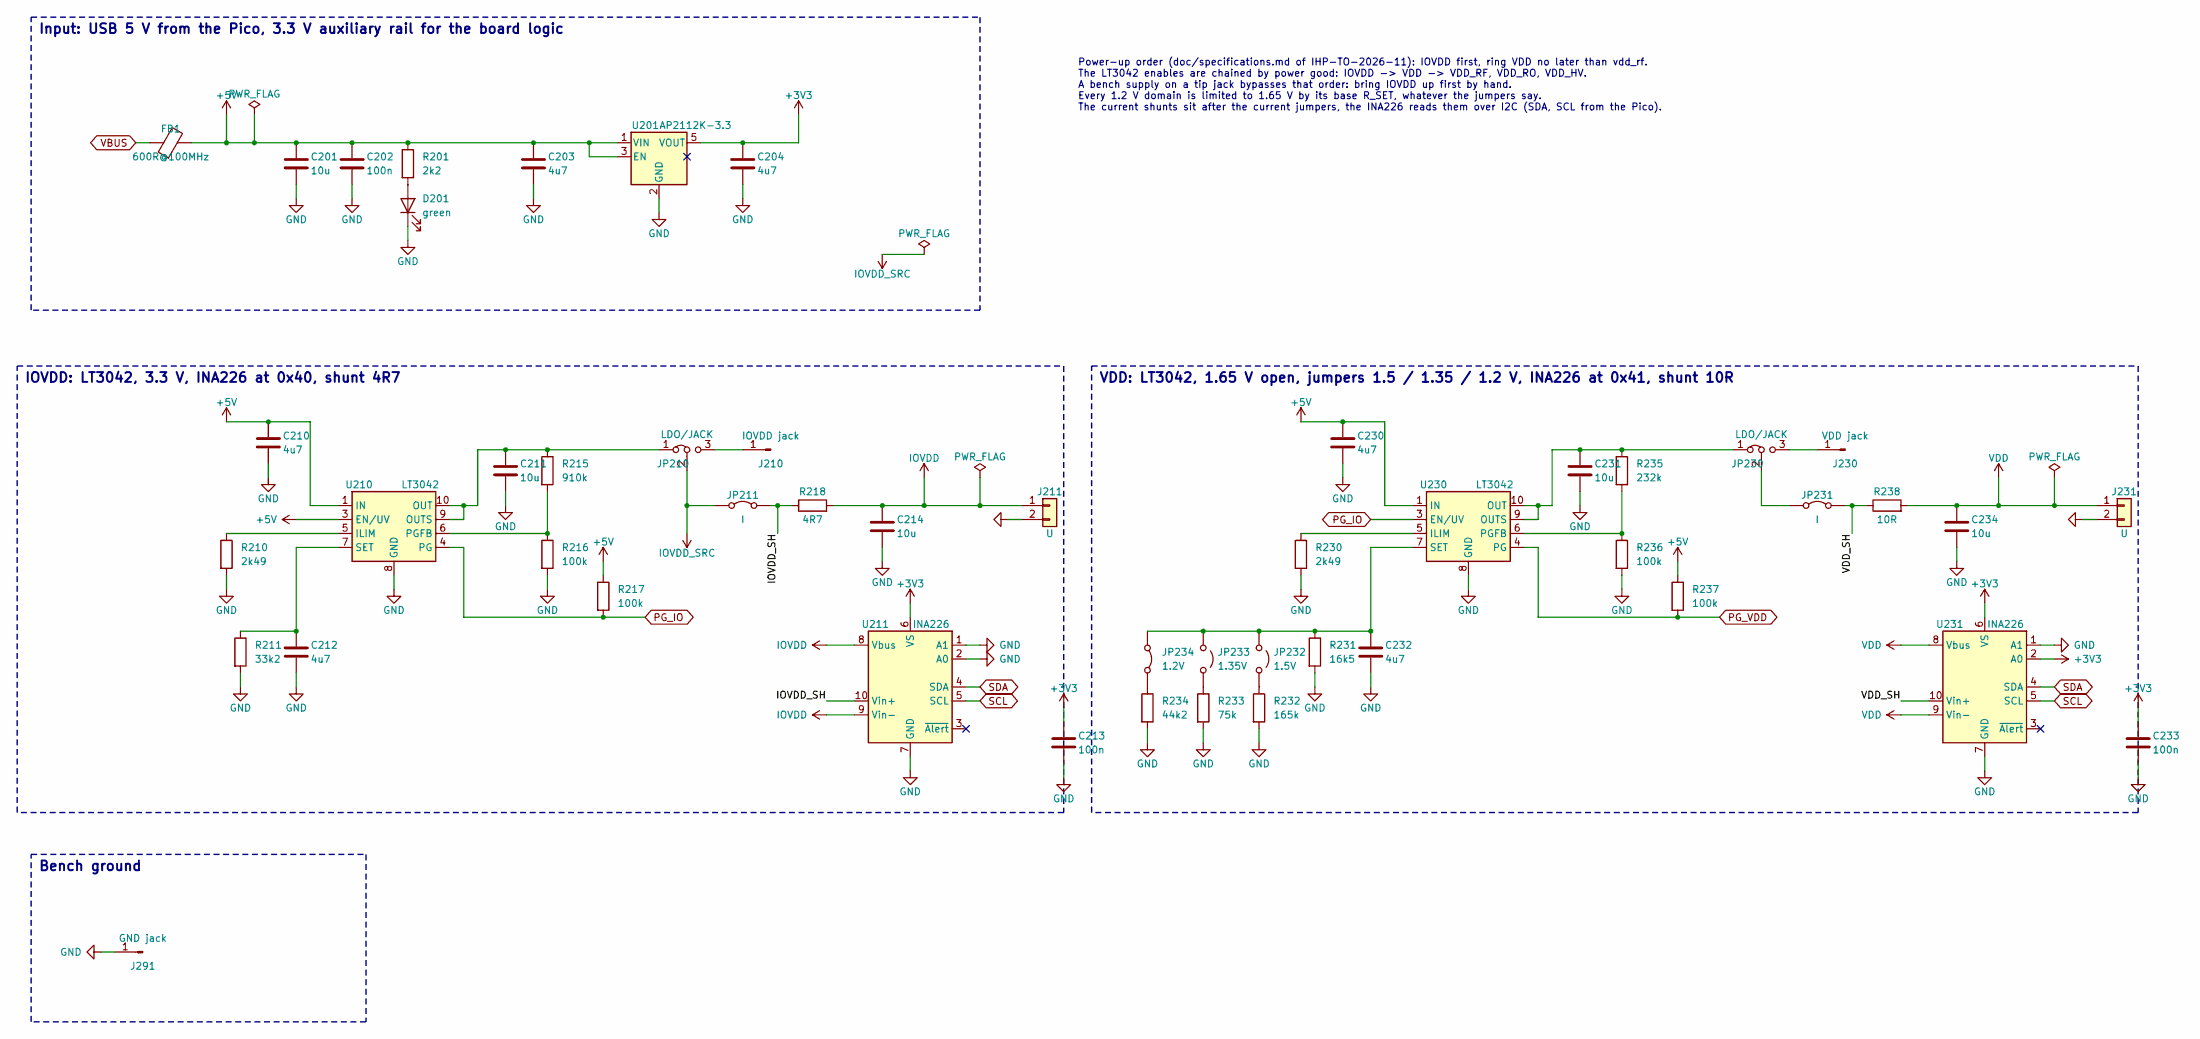
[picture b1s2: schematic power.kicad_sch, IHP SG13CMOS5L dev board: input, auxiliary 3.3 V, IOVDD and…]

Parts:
C201: 10u; C_1206_3216Metric_Pad1.33x1.80mm_HandSolder; MPN GRM31CR71E106KA12L
C202, C213, C233: 100n; C_0603_1608Metric_Pad1.08x0.95mm_HandSolder; MPN CL10B104KB8NNNC
C203, C204, C210, C212, C230, C232: 4u7; C_0805_2012Metric_Pad1.18x1.45mm_HandSolder; MPN CL21B475KOFNNNE
C211, C214, C231, C234: 10u; C_0805_2012Metric_Pad1.18x1.45mm_HandSolder; MPN CL21A106KOQNNNE
D201: green; LED_0603_1608Metric_Pad1.05x0.95mm_HandSolder; MPN APT1608LZGCK
FB1: 600R@100MHz; L_0603_1608Metric_Pad1.05x0.95mm_HandSolder; MPN BLM18KG601SN1D
J210: IOVDD jack; TipJack_Cinch_105-075x_Horizontal_P10.16mm_Yellow; MPN 105-0757-001
J211, J231: U; PinHeader_1x02_P2.54mm_Vertical
J230: VDD jack; TipJack_Cinch_105-075x_Horizontal_P10.16mm_Red; MPN 105-0752-001
J291: GND jack; TipJack_Cinch_105-075x_Horizontal_P10.16mm_Black; MPN 105-0753-001
JP210, JP230: LDO/JACK; PinHeader_1x03_P2.54mm_Vertical
JP211, JP231: I; PinHeader_1x02_P2.54mm_Vertical
JP232: 1.5V; PinHeader_1x02_P2.54mm_Vertical
JP233: 1.35V; PinHeader_1x02_P2.54mm_Vertical
JP234: 1.2V; PinHeader_1x02_P2.54mm_Vertical
R201: 2k2; R_0603_1608Metric_Pad0.98x0.95mm_HandSolder; MPN RC0603FR-072K2L
R210, R230: 2k49; R_0603_1608Metric_Pad0.98x0.95mm_HandSolder; MPN RC0603FR-072K49L
R211: 33k2; R_0603_1608Metric_Pad0.98x0.95mm_HandSolder; MPN RC0603FR-0733K2L
R215: 910k; R_0603_1608Metric_Pad0.98x0.95mm_HandSolder; MPN RC0603FR-07910KL
R216, R217, R236, R237: 100k; R_0603_1608Metric_Pad0.98x0.95mm_HandSolder; MPN RC0603FR-07100KL
R218: 4R7; R_0603_1608Metric_Pad0.98x0.95mm_HandSolder; MPN RC0603FR-074R7L
R231: 16k5; R_0603_1608Metric_Pad0.98x0.95mm_HandSolder; MPN RC0603FR-0716K5L
R232: 165k; R_0603_1608Metric_Pad0.98x0.95mm_HandSolder; MPN RC0603FR-07165KL
R233: 75k; R_0603_1608Metric_Pad0.98x0.95mm_HandSolder; MPN RC0603FR-0775KL
R234: 44k2; R_0603_1608Metric_Pad0.98x0.95mm_HandSolder; MPN RC0603FR-0744K2L
R235: 232k; R_0603_1608Metric_Pad0.98x0.95mm_HandSolder; MPN RC0603FR-07232KL
R238: 10R; R_0603_1608Metric_Pad0.98x0.95mm_HandSolder; MPN RC0603FR-0710RL
U201: AP2112K-3.3; SOT-23-5; MPN AP2112K-3.3TRG1
U210, U230: LT3042; MSOP-10-1EP_3x3mm_P0.5mm_EP1.68x1.88mm; MPN LT3042EMSE#PBF
U211, U231: INA226; TSSOP-10_3x3mm_P0.5mm; MPN INA226AIDGSR

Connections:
+3V3: C204.1, C213.1, C233.1, U201.5 (VOUT), U211.6 (VS), U231.2 (A0), U231.6 (VS); also elsewhere on the board
+5V: C201.1, C202.1, C203.1, C210.1, C230.1, FB1.2, R201.1, R217.1, R237.1, U201.1 (VIN), U201.3 (EN), U210.1 (IN), U210.2 (IN), U210.3 (EN/UV), U230.1 (IN), U230.2 (IN); also elsewhere on the board
/Power/IOVDD_SH: JP211.2 (B), R218.1, U211.10 (Vin+)
/Power/VDD_SH: JP231.2 (B), R238.1, U231.10 (Vin+)
GND: C201.2, C202.2, C203.2, C204.2, C210.2, C211.2, C212.2, C213.2, C214.2, C230.2, C231.2, C232.2, C233.2, C234.2, D201.1 (K), J211.2, J231.2, J291.1, R210.2, R211.2, R216.2, R230.2, R231.2, R232.2, R233.2, R234.2, R236.2, U201.2 (GND), U210.8 (GND), U210.11 (GND), U211.1 (A1), U211.2 (A0), U211.7 (GND), U230.8 (GND), U230.11 (GND), U231.1 (A1), U231.7 (GND); also elsewhere on the board
IOVDD: C214.1, J211.1, R218.2, U211.8 (Vbus), U211.9 (Vin-); also elsewhere on the board
IOVDD_SRC: JP210.2 (C), JP211.1 (A); also elsewhere on the board
unnamed: D201.2 (A), R201.2
unnamed: J210.1, JP210.3 (B)
unnamed: J230.1, JP230.3 (B)
unnamed: C211.1, JP210.1 (A), R215.1, U210.9 (OUTS), U210.10 (OUT)
unnamed: C231.1, JP230.1 (A), R235.1, U230.9 (OUTS), U230.10 (OUT)
unnamed: JP230.2 (C), JP231.1 (A)
unnamed: C232.1, JP232.1 (A), JP233.1 (A), JP234.1 (A), R231.1, U230.7 (SET)
unnamed: JP232.2 (B), R232.1
unnamed: JP233.2 (B), R233.1
unnamed: JP234.2 (B), R234.1
unnamed: R210.1, U210.5 (ILIM)
unnamed: R215.2, R216.1, U210.6 (PGFB)
unnamed: C212.1, R211.1, U210.7 (SET)
unnamed: R230.1, U230.5 (ILIM)
unnamed: R235.2, R236.1, U230.6 (PGFB)
PG_IO: R217.2, U210.4 (PG), U230.3 (EN/UV)
PG_VDD: R237.2, U230.4 (PG); also elsewhere on the board
SCL: U211.5 (SCL), U231.5 (SCL); also elsewhere on the board
SDA: U211.4 (SDA), U231.4 (SDA); also elsewhere on the board
VBUS: FB1.1; also elsewhere on the board
VDD: C234.1, J231.1, R238.2, U231.8 (Vbus), U231.9 (Vin-); also elsewhere on the board

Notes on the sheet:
Input: USB 5 V from the Pico, 3.3 V auxiliary rail for the board logic
Power-up order (doc/specifications.md of IHP-TO-2026-11): IOVDD first, ring VDD no later than vdd_rf. The LT3042 enables are chained by power good: IOVDD -> VDD -> VDD_RF, VDD_RO, VDD_HV. A bench supply on a tip jack bypasses that order: bring IOVDD up first by hand. Every 1.2 V domain is limited t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
IOVDD: LT3042, 3.3 V, INA226 at 0x40, shunt 4R7
VDD: LT3042, 1.65 V open, jumpers 1.5 / 1.35 / 1.2 V, INA226 at 0x41, shunt 10R
Bench ground

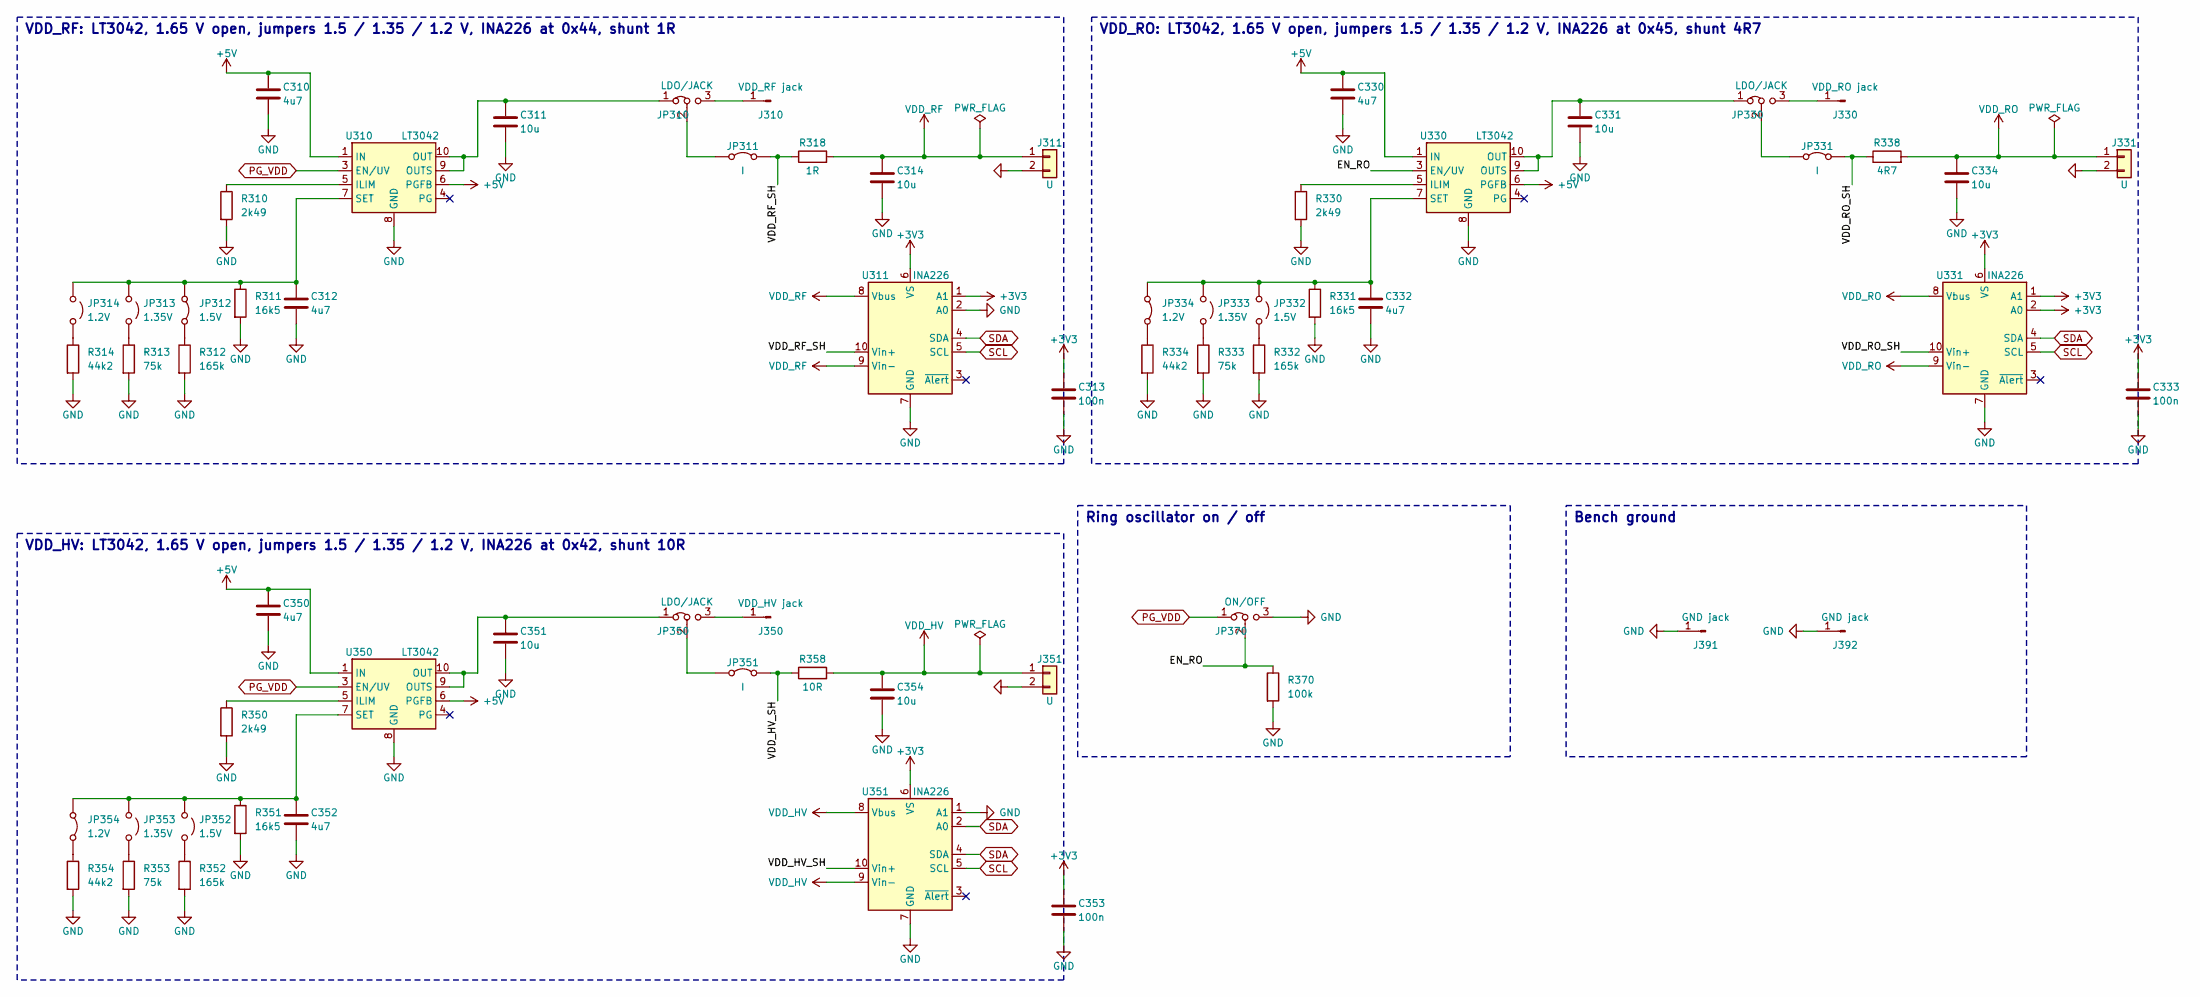
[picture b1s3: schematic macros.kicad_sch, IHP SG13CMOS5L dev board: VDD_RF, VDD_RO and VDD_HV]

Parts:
C310, C312, C330, C332, C350, C352: 4u7; C_0805_2012Metric_Pad1.18x1.45mm_HandSolder; MPN CL21B475KOFNNNE
C311, C314, C331, C334, C351, C354: 10u; C_0805_2012Metric_Pad1.18x1.45mm_HandSolder; MPN CL21A106KOQNNNE
C313, C333, C353: 100n; C_0603_1608Metric_Pad1.08x0.95mm_HandSolder; MPN CL10B104KB8NNNC
J310: VDD_RF jack; TipJack_Cinch_105-075x_Horizontal_P10.16mm_Red; MPN 105-0752-001
J311, J331, J351: U; PinHeader_1x02_P2.54mm_Vertical
J330: VDD_RO jack; TipJack_Cinch_105-075x_Horizontal_P10.16mm_Red; MPN 105-0752-001
J350: VDD_HV jack; TipJack_Cinch_105-075x_Horizontal_P10.16mm_Red; MPN 105-0752-001
J391, J392: GND jack; TipJack_Cinch_105-075x_Horizontal_P10.16mm_Black; MPN 105-0753-001
JP310, JP330, JP350: LDO/JACK; PinHeader_1x03_P2.54mm_Vertical
JP311, JP331, JP351: I; PinHeader_1x02_P2.54mm_Vertical
JP312, JP332, JP352: 1.5V; PinHeader_1x02_P2.54mm_Vertical
JP313, JP333, JP353: 1.35V; PinHeader_1x02_P2.54mm_Vertical
JP314, JP334, JP354: 1.2V; PinHeader_1x02_P2.54mm_Vertical
JP370: ON/OFF; PinHeader_1x03_P2.54mm_Vertical
R310, R330, R350: 2k49; R_0603_1608Metric_Pad0.98x0.95mm_HandSolder; MPN RC0603FR-072K49L
R311, R331, R351: 16k5; R_0603_1608Metric_Pad0.98x0.95mm_HandSolder; MPN RC0603FR-0716K5L
R312, R332, R352: 165k; R_0603_1608Metric_Pad0.98x0.95mm_HandSolder; MPN RC0603FR-07165KL
R313, R333, R353: 75k; R_0603_1608Metric_Pad0.98x0.95mm_HandSolder; MPN RC0603FR-0775KL
R314, R334, R354: 44k2; R_0603_1608Metric_Pad0.98x0.95mm_HandSolder; MPN RC0603FR-0744K2L
R318: 1R; R_0603_1608Metric_Pad0.98x0.95mm_HandSolder; MPN RC0603FR-071RL
R338: 4R7; R_0603_1608Metric_Pad0.98x0.95mm_HandSolder; MPN RC0603FR-074R7L
R358: 10R; R_0603_1608Metric_Pad0.98x0.95mm_HandSolder; MPN RC0603FR-0710RL
R370: 100k; R_0603_1608Metric_Pad0.98x0.95mm_HandSolder; MPN RC0603FR-07100KL
U310, U330, U350: LT3042; MSOP-10-1EP_3x3mm_P0.5mm_EP1.68x1.88mm; MPN LT3042EMSE#PBF
U311, U331, U351: INA226; TSSOP-10_3x3mm_P0.5mm; MPN INA226AIDGSR

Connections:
+3V3: C313.1, C333.1, C353.1, U311.1 (A1), U311.6 (VS), U331.1 (A1), U331.2 (A0), U331.6 (VS), U351.6 (VS); also elsewhere on the board
+5V: C310.1, C330.1, C350.1, U310.1 (IN), U310.2 (IN), U310.6 (PGFB), U330.1 (IN), U330.2 (IN), U330.6 (PGFB), U350.1 (IN), U350.2 (IN), U350.6 (PGFB); also elsewhere on the board
/Macro supplies/EN_RO: JP370.2 (C), R370.1, U330.3 (EN/UV)
/Macro supplies/VDD_HV_SH: JP351.2 (B), R358.1, U351.10 (Vin+)
/Macro supplies/VDD_RF_SH: JP311.2 (B), R318.1, U311.10 (Vin+)
/Macro supplies/VDD_RO_SH: JP331.2 (B), R338.1, U331.10 (Vin+)
GND: C310.2, C311.2, C312.2, C313.2, C314.2, C330.2, C331.2, C332.2, C333.2, C334.2, C350.2, C351.2, C352.2, C353.2, C354.2, J311.2, J331.2, J351.2, J391.1, J392.1, JP370.3 (B), R310.2, R311.2, R312.2, R313.2, R314.2, R330.2, R331.2, R332.2, R333.2, R334.2, R350.2, R351.2, R352.2, R353.2, R354.2, R370.2, U310.8 (GND), U310.11 (GND), U311.2 (A0), U311.7 (GND), U330.8 (GND), U330.11 (GND), U331.7 (GND), U350.8 (GND), U350.11 (GND), U351.1 (A1), U351.7 (GND); also elsewhere on the board
unnamed: J310.1, JP310.3 (B)
unnamed: J330.1, JP330.3 (B)
unnamed: J350.1, JP350.3 (B)
unnamed: C311.1, JP310.1 (A), U310.9 (OUTS), U310.10 (OUT)
unnamed: JP310.2 (C), JP311.1 (A)
unnamed: C312.1, JP312.1 (A), JP313.1 (A), JP314.1 (A), R311.1, U310.7 (SET)
unnamed: JP312.2 (B), R312.1
unnamed: JP313.2 (B), R313.1
unnamed: JP314.2 (B), R314.1
unnamed: C331.1, JP330.1 (A), U330.9 (OUTS), U330.10 (OUT)
unnamed: JP330.2 (C), JP331.1 (A)
unnamed: C332.1, JP332.1 (A), JP333.1 (A), JP334.1 (A), R331.1, U330.7 (SET)
unnamed: JP332.2 (B), R332.1
unnamed: JP333.2 (B), R333.1
unnamed: JP334.2 (B), R334.1
unnamed: C351.1, JP350.1 (A), U350.9 (OUTS), U350.10 (OUT)
unnamed: JP350.2 (C), JP351.1 (A)
unnamed: C352.1, JP352.1 (A), JP353.1 (A), JP354.1 (A), R351.1, U350.7 (SET)
unnamed: JP352.2 (B), R352.1
unnamed: JP353.2 (B), R353.1
unnamed: JP354.2 (B), R354.1
unnamed: R310.1, U310.5 (ILIM)
unnamed: R330.1, U330.5 (ILIM)
unnamed: R350.1, U350.5 (ILIM)
PG_VDD: JP370.1 (A), U310.3 (EN/UV), U350.3 (EN/UV); also elsewhere on the board
SCL: U311.5 (SCL), U331.5 (SCL), U351.5 (SCL); also elsewhere on the board
SDA: U311.4 (SDA), U331.4 (SDA), U351.2 (A0), U351.4 (SDA); also elsewhere on the board
VDD_HV: C354.1, J351.1, R358.2, U351.8 (Vbus), U351.9 (Vin-); also elsewhere on the board
VDD_RF: C314.1, J311.1, R318.2, U311.8 (Vbus), U311.9 (Vin-); also elsewhere on the board
VDD_RO: C334.1, J331.1, R338.2, U331.8 (Vbus), U331.9 (Vin-); also elsewhere on the board

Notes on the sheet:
VDD_RF: LT3042, 1.65 V open, jumpers 1.5 / 1.35 / 1.2 V, INA226 at 0x44, shunt 1R
VDD_RO: LT3042, 1.65 V open, jumpers 1.5 / 1.35 / 1.2 V, INA226 at 0x45, shunt 4R7
VDD_HV: LT3042, 1.65 V open, jumpers 1.5 / 1.35 / 1.2 V, INA226 at 0x42, shunt 10R
Ring oscillator on / off
Bench ground

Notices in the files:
README.md:
License:
Licensed under the **Solderpad Hardware License v2.1**, see [`LICENSE`](LICENSE).
License: Solderpad Hardware License v2.1
Cite This Work
